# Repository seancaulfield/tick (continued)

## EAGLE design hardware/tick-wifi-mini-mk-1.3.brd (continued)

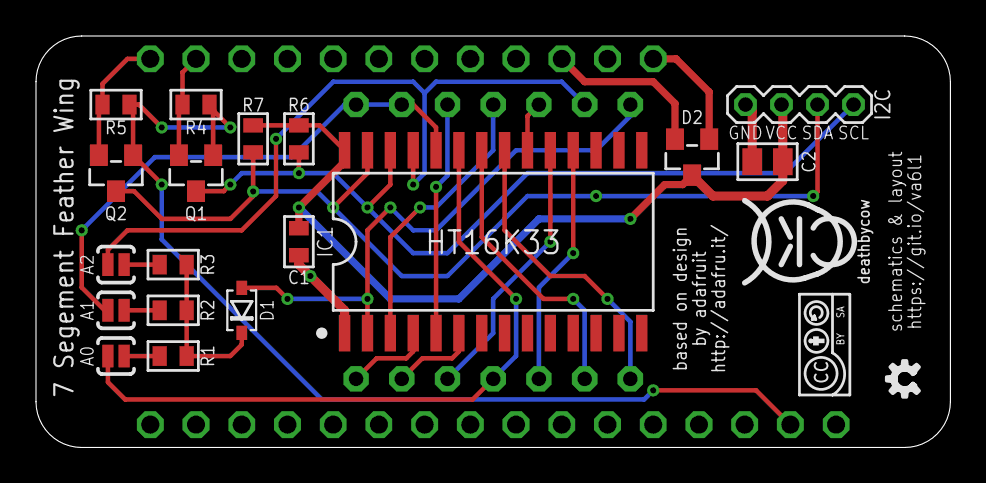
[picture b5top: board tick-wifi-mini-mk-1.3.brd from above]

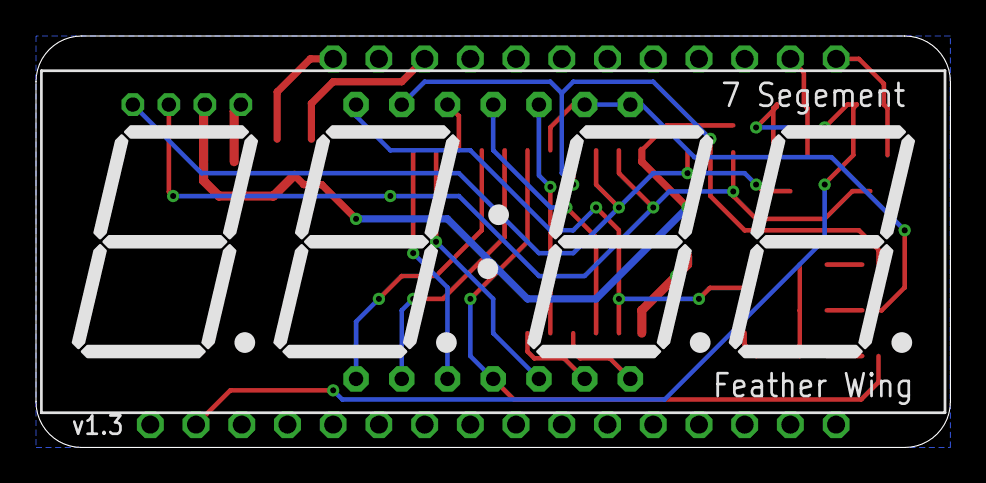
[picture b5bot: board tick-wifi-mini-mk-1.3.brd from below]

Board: 2 copper layers, 50.8 x 22.9 mm, 24 parts (2 on the bottom side), 26 nets.

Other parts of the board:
U$2: COW_SMALL
U$3: OSHWLOGO_TINY_SILKONLY
U$4: CC-BY-SA-4.0-NO-URL

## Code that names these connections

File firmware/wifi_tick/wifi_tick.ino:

/*
 * wifi_tick.ino - NTP-ified T.I.C.K.
 *
 * Author:  Sean Caulfield <sean@yak.net>
 * License: GPLv2
 *
 */

#include <SPI.h>
#include <Wire.h>

#include <LedControl.h>
#include <RTClib.h>
#include <DS3231.h>
#include <Time.h>
#include <Timezone.h>

#include <ESP8266WiFi.h>
#include <ESP8266WiFiMulti.h>
#include <WiFiUdp.h>
#include <NTPClient.h>
#include <ESP8266WebServer.h>

#include <string.h>

#include "debug.h"
#include "config.h"

//
// Display pin assignments & settings
//

#define DISP_DATA      13
#define DISP_CLCK      14
#define DISP_LOAD      12
#define DISP_NUM        2
#define BRIGHT_LARGE   15
#define BRIGHT_SMALL    5

// Maximum diff between NTP and RTC before adjusting the RTC to match
#define MAX_TIME_DIFF   5

// Admin web server port
#define HTTP_PORT 80

inline uint32_t usec_diff(uint32_t a, uint32_t b) {
  if (a > b) {
    return a - b;
  } else {
    return b - a;
  }
}

//
// Global controls/vars
//

WiFiUDP ntpUDP;
NTPClient ntpclient(ntpUDP);
ESP8266WebServer server(HTTP_PORT);
LedControl display = LedControl(DISP_DATA, DISP_CLCK, DISP_LOAD, DISP_NUM);
RTC_DS3231 rtc;

uint32_t ntp_time = 0;
uint32_t rtc_time = 0;
DateTime dt_utc;
DateTime dt_local;

boolean firstConnected = false;
boolean httpServerSetup = false;

//
// Timezones - These are hard coded for now, but plan is to try to support
// actual TZ files, and hopefully automatically download & update them.
//

TimeChangeRule est = {"EST", First,  Sun, Nov, 2, -5*60};
TimeChangeRule edt = {"EDT", Second, Sun, Mar, 2, -4*60};
Timezone tz = Timezone(edt, est);

////////////////////////////////////////////////////////////////////////////////

//
// Handle the network stuff so it can be disabled in case wifi isn't available.
//
void handle_net() {

  // Get current time from NTP. Has its own internal check to only poll every
  // 60s so we're not blasting the NTP pool servers.
  ntpclient.update();

  // Get current time
  ntp_time = ntpclient.getEpochTime();

  // Handle any web serving we're supposed to be doing
  if (httpServerSetup) {
    server.handleClient();
  }

}

//
// Refresh global time variable from whichever source we've got.
//
void refresh_time() {

  // Get current time from RTC
  rtc_time = rtc.now().unixtime();

  // Update global local & UTC datetime objects with NTP if it's available and
  // the RTC otherwise.
  if (ntpclient.isValidYet()) {
    dt_utc.setTime(ntp_time);
    dt_local.setTime(tz.toLocal(ntp_time));
  } else {
    dt_utc.setTime(rtc_time);
    dt_local.setTime(tz.toLocal(rtc_time));
  }

  // Set RTC if it looks like it's not been set and set it if not.
  if (ntpclient.isValidYet() && usec_diff(ntp_time, rtc_time) > MAX_TIME_DIFF) {
    rtc.adjust(dt_utc);
  }

  //DPRINTLN(dt_utc.iso8601());
  //DPRINTLN(dt_local.iso8601());

}

//
// Refresh display with current local time (from global var).
//
void refresh_display() {

  // Refresh large display (HH:MM). Try to emulate colon by setting decimal on
  // middle digits.
  display.clearDisplay(0);
  if (dt_local.hour() >= 10)
    display.setDigit(0, 0, dt_local.hour() / 10, false);
  display.setDigit(0, 1, dt_local.hour() % 10, true);
  display.setDigit(0, 2, dt_local.minute() / 10, true, true);
  display.setDigit(0, 3, dt_local.minute() % 10, false, true);

  // Refresh small displays (YYYY MM DD)
  display.clearDisplay(1);
  display.setDigit(1, 0, dt_local.month() / 10, false);
  display.setDigit(1, 1, dt_local.month() % 10, true);
  display.setDigit(1, 2, dt_local.day() / 10, false);
  display.setDigit(1, 3, dt_local.day() % 10, false);
  display.setDigit(1, 4, dt_local.year() / 1000, false);
  display.setDigit(1, 5, (dt_local.year() / 100) % 10, false);
  display.setDigit(1, 6, (dt_local.year() / 10) % 10, false);
  display.setDigit(1, 7, dt_local.year() % 10, true);

}

//
// Setup routing to callbacks for web server (but only if we've got wifi)
//
void setup_server() {
  // TODO
}

////////////////////////////////////////////////////////////////////////////////

//
// SETUP() - This is done once at startup.
//

void setup() {

#if (DEBUG)
  delay(200);
  Serial.begin(SERIAL_BAUD);
  delay(10);
#endif

  //
  // Setup large digit display. Have to set the scan limit as it's only 4
  // digits (but we'll be pushing the chip a bit because each segment is
  // actually 2 LEDs).
  //

  display.shutdown(0, false);
  display.setScanLimit(0, 4);
  display.setIntensity(0, BRIGHT_LARGE);
  display.clearDisplay(0);

  //
  // Setup small digit displays.
  //

  display.shutdown(1, false);
  display.setIntensity(1, BRIGHT_SMALL);
  display.clearDisplay(1);

  //
  // Setup RTC
  //
  Wire.begin();
  if (rtc.begin() && !rtc.isrunning()) {
    rtc.enable();
  }

  //
  // Connect to Wifi. Not bothering to check if it's ready as that's done in
  // the main loop (as the gate for doing network-related stuff).
  //

  DPRINTLN("Connecting to wifi"); DFLUSH();
  WiFi.begin(MY_WIFI_SSID, MY_WIFI_PASS);

}

//
// LOOP() - This is done lots, like your mom.
//

void loop() {

  // Update time & display
  refresh_time();
  refresh_display();

  // Check if Wifi is connected and if so, handle networking stuff
  if (WiFi.status() == WL_CONNECTED) {
    if (!firstConnected) {
      firstConnected = true;
      DPRINT("Connected to wifi! IP ");
      DPRINTLN(WiFi.localIP());
      ntpclient.begin();
      boolean result = ntpclient.forceUpdate();
      DPRINT("NTP result = ");
      DPRINTLN(result);
      DPRINTLN(ntp_time);
      setup_server();
    }
    handle_net();
  }

  delay(1000);
  //yield();

}

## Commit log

2014-12-15 initialization commit
2014-12-19 shift register based version
2014-12-20 scaled down even more
2015-01-23 again with the not sure what the fuck i was thinking
2015-01-23 look clocks are hard
2015-02-16 tinkering with shit
2015-02-16 charlieplexing shield attempt
2015-02-17 shieldify all the things
2015-02-19 going for a fully integrated board now using charlieplexing
2015-02-20 routed and RTC chip added
2015-02-20 adding onboard regulator
2015-02-21 swapping most SMD components to PTH ones except for the ICs
2015-02-22 layout complete for rev 4.2
2015-02-22 rev 4.3 tweaked i2c lines and replaced resonator with crystal and caps
2015-02-22 branching a new version to use a different core chip type (pth based probably)
2015-02-22 pth version done, way easier than expected
2015-02-23 smt barrels of fun
2015-02-23 reverting v4.4 and adding 4.6 for compromise between saner layout and all pth/on-hand parts design
2015-02-23 i unno
2015-02-23 twiddled with dimensions to fit a hammond 1591XXC enclosure
2015-02-23 redoing YET AGAIN going back to the max7219 chips i have an asston of
2015-02-24 diddling
2015-02-25 commit before pull
2015-02-27 more layout tinkering for the max7129 soic version. broke out into a board with only the two display drivers on it for now, will add other componets once this layout part is done.
2015-02-28 relayout of pth version using only atmega for charlieplexing
2015-02-28 adding second ground plane to bottom layer and tweaking a few lines on the silkscreen layer
2015-02-28 yet another redo, this time to swap to using UART/arduino for code uploading (so I can use that to synchronize the time) and to free up an analog pin to read the backup battery level
2015-03-01 nets complete, now for layout
2015-03-02 layout done but still need to add battery monitoring circuit
2015-03-03 resistor divider to check battery level
2015-03-04 finished this layout changed my mind again
2015-03-04 throwing a ds3231s at the problem
2015-03-05 think i'm done fiddling
2015-03-05 nope, switching to 0.1in headers for ftdi conn
2015-03-05 headers swapped, layout de-fucked a bit more
2015-03-06 tweaks to silkscreen and traces
2015-03-06 more bottom silk tweaks since oshpark isn't rendering the board right
2015-03-06 description update and further widening of bottom silk layer vector graphics in case that's oshapark's problem
2015-03-06 project reorg, changing to makefile instead of ino for better low level support and saner lib handling, expanding to atmega support for tick hw mk 4.6.4
2015-03-06 missed this one
2015-03-06 adding forked RTCLib as submodule
2015-03-09 ugh, apparently the makefile refuses to find my lib code now
2015-03-09 a whole bunch of versions and not sure which work. check 'em all in and sort it out later
2015-03-09 removing rtclib submodule for now
2015-03-10 well that made it work for now, but ugh, need to fix this
2015-03-10 move includes back to header file
2015-03-16 clocks are hard, some more stabs
2015-03-16 clocks are hard, some more stabs pt 2 the electric buggering
2015-03-17 more shit for my shitty self
2015-03-17 alskdfjasdlfj
2015-03-20 more attempts at a hammond 1591A sized clock
2015-03-21 lasikdfjalsdjf
2015-03-21 layout done
2015-03-22 reorganizing firmware to have a few different variants for the boards
2015-03-22 charlieplexing test firmware
2015-03-22 exclude some build directories and unnamed vim swapfiles
2015-03-22 more layout tweaks for smt design
2015-03-22 Fixes: RX/TX swapped, RST disconnected, UART moved.
2015-03-22 shuffle duffle
2015-03-22 renames are hard
2015-04-08 microsecond utility header
2015-05-11 more charlieplexing FAIL code
2015-05-26 another fucking miniversion
2015-05-26 description crap
2015-05-27 more twiddling and otherwise not making progress
2015-06-22 i swear i will make this sucker work
2015-07-18 more versions
2015-08-10 ds3231 breakouts
2015-08-10 more boards
2015-11-30 new versions for reasons
2015-12-01 new board using adafruit metro
2016-02-06 initial commit of esp8266 based version
2016-02-07 version to use feather
2016-02-07 initial firmware commit
2016-02-07 fix some derp my-C-is-soooo-rusty mistakes
2016-02-08 out of fucks for today
2016-02-10 layout finished for wifail board
2016-02-27 new board
2016-02-27 poc for ht16k33 i2c display controller operating at 3.3V
2016-03-02 design for esp8266 huzzah i2d 7 segment display using ht16k33-28
2016-03-18 updates:
2016-03-18 two new revisions, but only 1.2 will work b/c i'm a moron
2016-04-30 ugh debugging
2016-07-01 getting it to work
2016-07-01 new hw rev
2016-07-01 firmware to set DS1307 and DS3231 i2c RTCs using NTP data
2016-07-02 wasn't going to use it after all
2016-07-04 working auto-setter for ds3231's!
2016-07-19 more wip
2016-07-20 more wip again
2016-07-26 new tick version
2016-07-26 dicking around with layouts
2016-08-18 how did this not get commited before?
2016-08-19 yet another attempt at a ht16k33 driver
2016-08-26 working, supports hardcoded timezones
2016-08-26 fucking silkscreen error--flipped CLK and DAT markings
2016-09-07 wip esp8266 mods
2016-09-07 add RTC gettting & setting
2016-10-11 renamed appropriately
2016-10-11 will the real tinytick please stand up. no, higher. oh, right.
2017-05-29 more bored boards
2017-05-29 working maybe?
2017-05-29 code for rpi based tick with custom pcb
2017-05-31 add ht16k33 i2c version
2017-06-13 more stuff for pi
2017-06-15 working rpi using ht16k33
2017-06-15 actually install clock script
2017-07-01 moar boards
2017-09-30 added retry logic around i2c errors
2017-10-02 wip omg
2017-10-03 wip still
2017-11-02 more pi boards
2017-11-02 backport this overlay from the 4.9 RPi tree for my usage here
2017-11-02 change to building using gpio-shutdown-overlay
2017-11-08 backwards?
2017-11-09 blank display on shutdown, update udev rules for shutdown button
2017-11-09 remove my crappy devicetree failures
2017-11-09 rename trigger to something more/less appro
2017-11-09 i want some text farted when i push it
2017-11-09 cleanup code
2017-11-09 seems to work slightly better?
2019-09-15 cleanup dangling symlinks
2019-09-15 add setup script for RPi SD cards
2019-09-15 add dtoverlays for shutdown
2019-09-16 authorized_keys file to right dir derp
2019-09-26 now with (gag) systemd support
2019-09-26 more tinkering for buster
2019-09-27 fix issue where keeps blinking after signal
2022-09-10 notes/setup script for making GPS clock v2.0
2022-11-24 updates for python3, new libs, etc
2022-11-24 install to usr/local
2022-11-24 requirements, change shebang
2022-11-24 update install and service
2022-11-24 no need to remove the service file
